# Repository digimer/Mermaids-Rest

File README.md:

# Mermaids-Rest

All tools for the Mermaid's Rest open sailing tools

*Note*: Patches and PRs are welcome, but at this stage of the project, I need to be able to understand / fix the code. Good comments and references to reading material will be grately appreciated! ^_^ 

If/when the project gets outside interest, I'll step out of the way of the much more talented folks.

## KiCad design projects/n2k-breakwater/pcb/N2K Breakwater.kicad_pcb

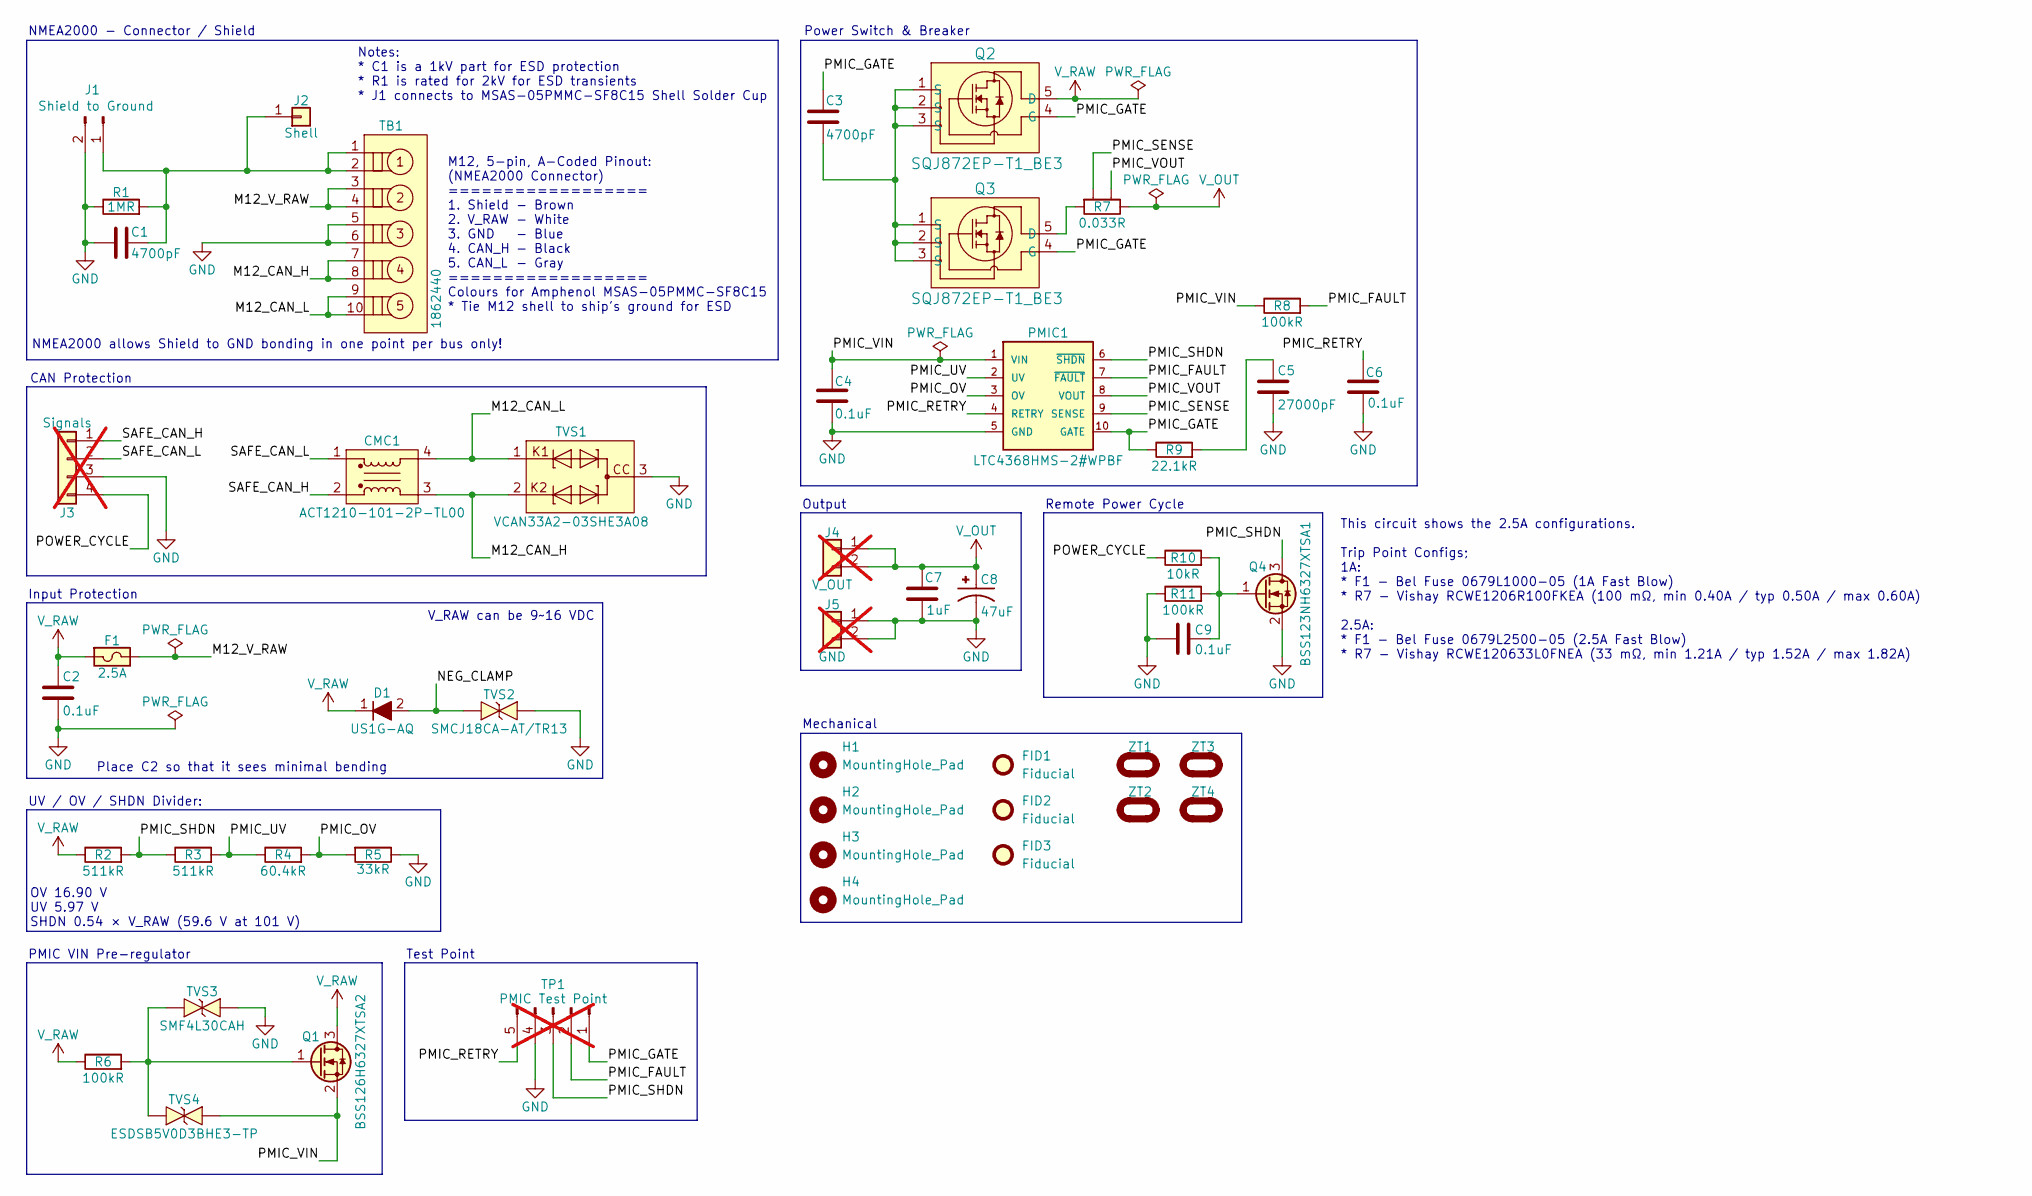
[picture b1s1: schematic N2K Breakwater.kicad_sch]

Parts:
C1, C3: 4700pF; Murata GCJ31BR73A; Part Murata GCJ31BR73A472KXJ1L
C2: 0.1uF; TDK CGA5; Part TDK CGA5L3X7R2E104K160AE
C4, C6, C9: 0.1uF; Kyocera AVX 0805; Part Kyocera 08051C104K4Z2A
C5: 27000pF; Murata GCM0805; Part Murata GCM21B5C2A273JE02K
C7: 1uF; Kyocera AVX 0805; Part Kyocera 08051C105K4Z2A
C8: 47uF; Nichicon PCM; Part Nichicon PCM1V470MCL1GS
CMC1: ACT1210-101-2P-TL00; TDK ACT12101012PTL00; Part TDK ACT1210-101-2P-TL00
D1: US1G-AQ; Diotec US1G; Part Diotec US1G-AQ
F1: 2.5A; Bel Fuse 0679L; Part Bel Fuse 0679L2500-05
FID1, FID2, FID3: Fiducial; Fiducial_1mm_Mask2mm
H1, H2, H3, H4: MountingHole_Pad; MountingHole_4mm
J1: Shield to Ground; PinHeader_1x02_P2.54mm_Vertical
J2: Shell; PinHeader_1x01_P2.54mm_Vertical
J3: Signals; PinHeader_1x04_P2.54mm_Vertical; not fitted
J4: V_OUT; PinHeader_1x02_P2.54mm_Vertical; not fitted
J5: GND; PinHeader_1x02_P2.54mm_Vertical; not fitted
PMIC1: LTC4368HMS-2#WPBF; ADI LTC4368; Part ADI LTC4368HMS-2#WPBF
Q1: BSS126H6327XTSA2; Infineon BSS126; Part Infineon BSS126H6327XTSA2
Q2, Q3: SQJ872EP-T1_BE3; Vishay SQJ872EP; Part Vishay SQJ872EP-T1_BE3
Q4: BSS123NH6327XTSA1; Infineon BSS123; Part Infineon BSS123NH6327XTSA1
R1: 1MR; Stackpole RMCA0805; Part Stackpole RMCA0805FT1M00-HP
R2, R3: 511kR; Vishay RCA e3; Part Vishay RCA0603511KFKEA
R4: 60.4kR; Vishay RCA-SR e3; Part Vishay RCA080560K4FKEA
R5: 33kR; Stackpole RMCA0603; Part Stackpole RMCA0603FT33K0-HP
R6, R8, R11: 100kR; Stackpole RMCA0805; Part Stackpole RMCA0805FT100K-HP
R7: 0.033R; Vishay RCWE 1206 4-wire Kelvin; Part Vishay RCWE120633L0FNEA
R9: 22.1kR; Stackpole RNCP0805; Part Stackpole RNCP0805FTD22K1
R10: 10kR; Stackpole RNCP0805; Part Stackpole RNCP0805FTD10K0
TB1: 1862440; Phoenix Contact 1862440; Part Phoenix Contact 1862440
TP1: PMIC Test Point; PinHeader_1x05_P2.54mm_Vertical; not fitted
TVS1: VCAN33A2-03SHE3A08; Vishay VCAN33A2-03S; Part Vishay VCAN33A2-03SHE3A08
TVS2: SMCJ18CA-AT/TR13; Yageo DO-214AB; Part Yageo SMCJ18CA-AT/TR13
TVS3: SMF4L30CAH; TSC SMF4L30CAH; Part TSC SMF4L30CAH
TVS4: ESDSB5V0D3BHE3-TP; MCC ESDSB5V0D3; Part MCC ESDSB5V0D3BHE3-TP
ZT1, ZT2, ZT3, ZT4: Tuskar Ziptie Slot 4.5x2mm

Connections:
/M12_CAN_H: CMC1.3 (O2), TB1.7, TB1.8, TVS1.2
/M12_CAN_L: CMC1.4 (O1), TB1.9, TB1.10, TVS1.1
/M12_V_RAW: F1.2, TB1.3, TB1.4
/NEG_CLAMP: D1.2 (A), TVS2.1
/PMIC_FAULT: PMIC1.7 (~FAULT), R8.2, TP1.2
/PMIC_GATE: C3.2, PMIC1.10 (GATE), Q2.4 (G), Q3.4 (G), R9.1, TP1.1
/PMIC_OV: PMIC1.3 (OV), R4.2, R5.1
/PMIC_RETRY: C6.2, PMIC1.4 (RETRY), TP1.5
/PMIC_SENSE: PMIC1.9 (SENSE), R7.3
/PMIC_SHDN: PMIC1.6 (~SHDN), Q4.3 (D), R2.2, R3.1, TP1.3
/PMIC_UV: PMIC1.2 (UV), R3.2, R4.1
/PMIC_VIN: C4.1, PMIC1.1 (VIN), Q1.2 (S), R8.1, TVS4.2
/PMIC_VOUT: PMIC1.8 (VOUT), R7.4
/POWER_CYCLE: J3.4, R10.1
/SAFE_CAN_H: CMC1.2 (I2), J3.1
/SAFE_CAN_L: CMC1.1 (I1), J3.2
GND: C1.1, C2.2, C4.2, C5.2, C6.1, C7.2, C8.2, C9.1, J1.2, J3.3, J5.1, J5.2, PMIC1.5 (GND), Q4.2 (S), R1.1, R5.2, R11.1, TB1.5, TB1.6, TP1.4, TVS1.3, TVS2.2, TVS3.2
unnamed: C3.1, Q2.1 (S), Q2.2 (S), Q2.3 (S), Q3.1 (S), Q3.2 (S), Q3.3 (S)
unnamed: C5.1, R9.2
unnamed: C1.2, J1.1, J2.1 (Pin_1_1), R1.2, TB1.1, TB1.2
unnamed: Q1.1 (G), R6.2, TVS3.1, TVS4.1
unnamed: Q3.5 (D), R7.1
unnamed: C9.2, Q4.1 (G), R10.2, R11.2
V_OUT: C7.1, C8.1, J4.1, J4.2, R7.2
V_RAW: C2.1, D1.1 (K), F1.1, Q1.3 (D), Q2.5 (D), R2.1, R6.1

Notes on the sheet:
Remote Power Cycle
CAN Protection
This circuit shows the 2.5A configurations. Trip Point Configs; 1A: * F1 - Bel Fuse 0679L1000-05 (1A Fast Blow) * R7 - Vishay RCWE1206R100FKEA (100 mΩ, min 0.40A / typ 0.50A / max 0.60A) 2.5A: * F1 - Bel Fuse 0679L2500-05 (2.5A Fast Blow) * R7 - Vishay RCWE120633L0FNEA (33 mΩ, min 1.21A / typ 1.52A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
V_RAW can be 9~16 VDC
PMIC VIN Pre-regulator
Output
Notes: * C1 is a 1kV part for ESD protection * R1 is rated for 2kV for ESD transients * J1 connects to MSAS-05PMMC-SF8C15 Shell Solder Cup
M12, 5-pin, A-Coded Pinout: (NMEA2000 Connector) ================== 1. Shield 2. V_RAW 3. GND 4. CAN_H 5. CAN_L ================== Colours for Amphenol MSAS-05PMMC-SF8C15 * Tie M12 shell to ship's ground for ESD
Input Protection
Power Switch & Breaker
UV / OV / SHDN Divider:
Place C2 so that it sees minimal bending
NMEA2000 - Connector / Shield
Mechanical
NMEA2000 allows Shield to GND bonding in one point per bus only!
OV 16.90 V UV 5.97 V SHDN 0.54 × V_RAW (59.6 V at 101 V)
- Brown - White - Blue - Black - Gray
Test Point

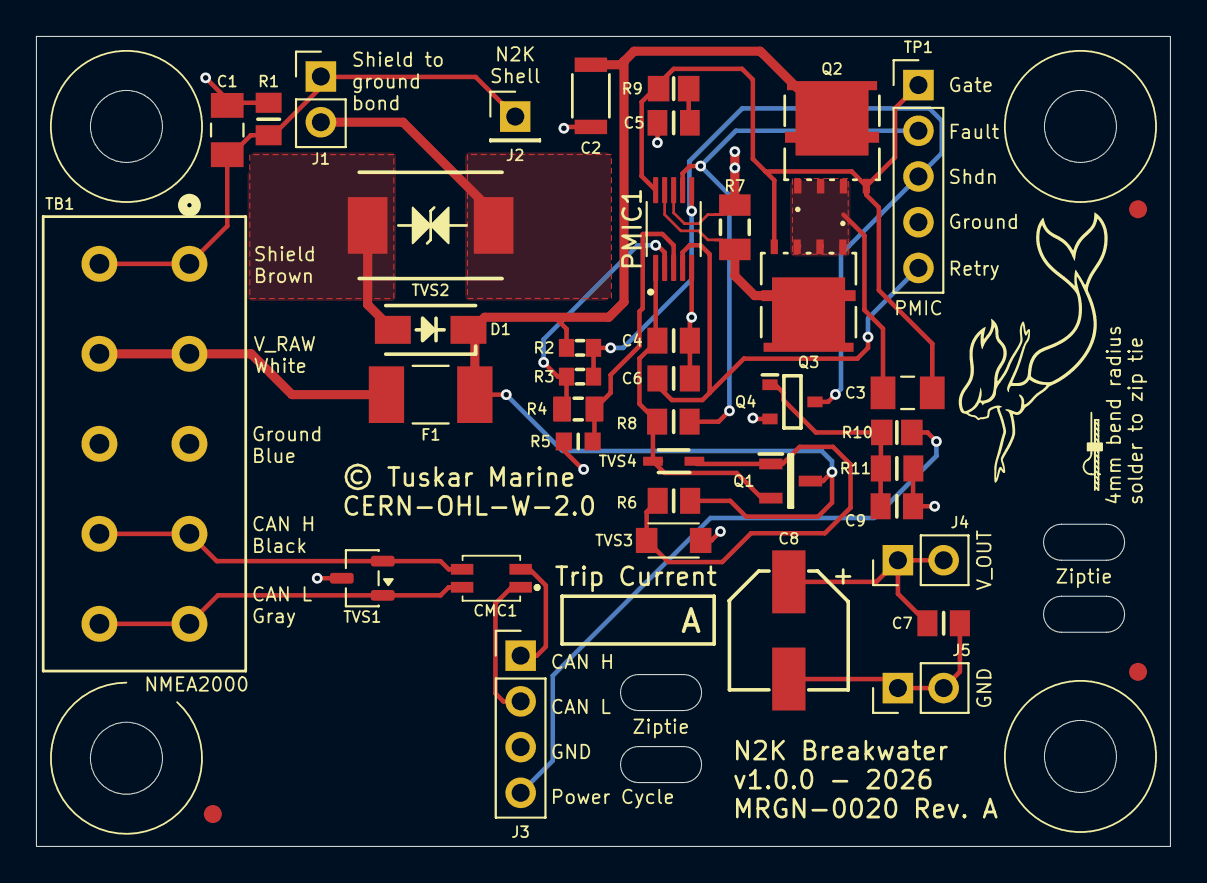
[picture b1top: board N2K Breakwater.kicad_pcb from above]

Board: 4 copper layers, 63.0 x 45.0 mm, 50 parts (0 on the bottom side), 25 nets.

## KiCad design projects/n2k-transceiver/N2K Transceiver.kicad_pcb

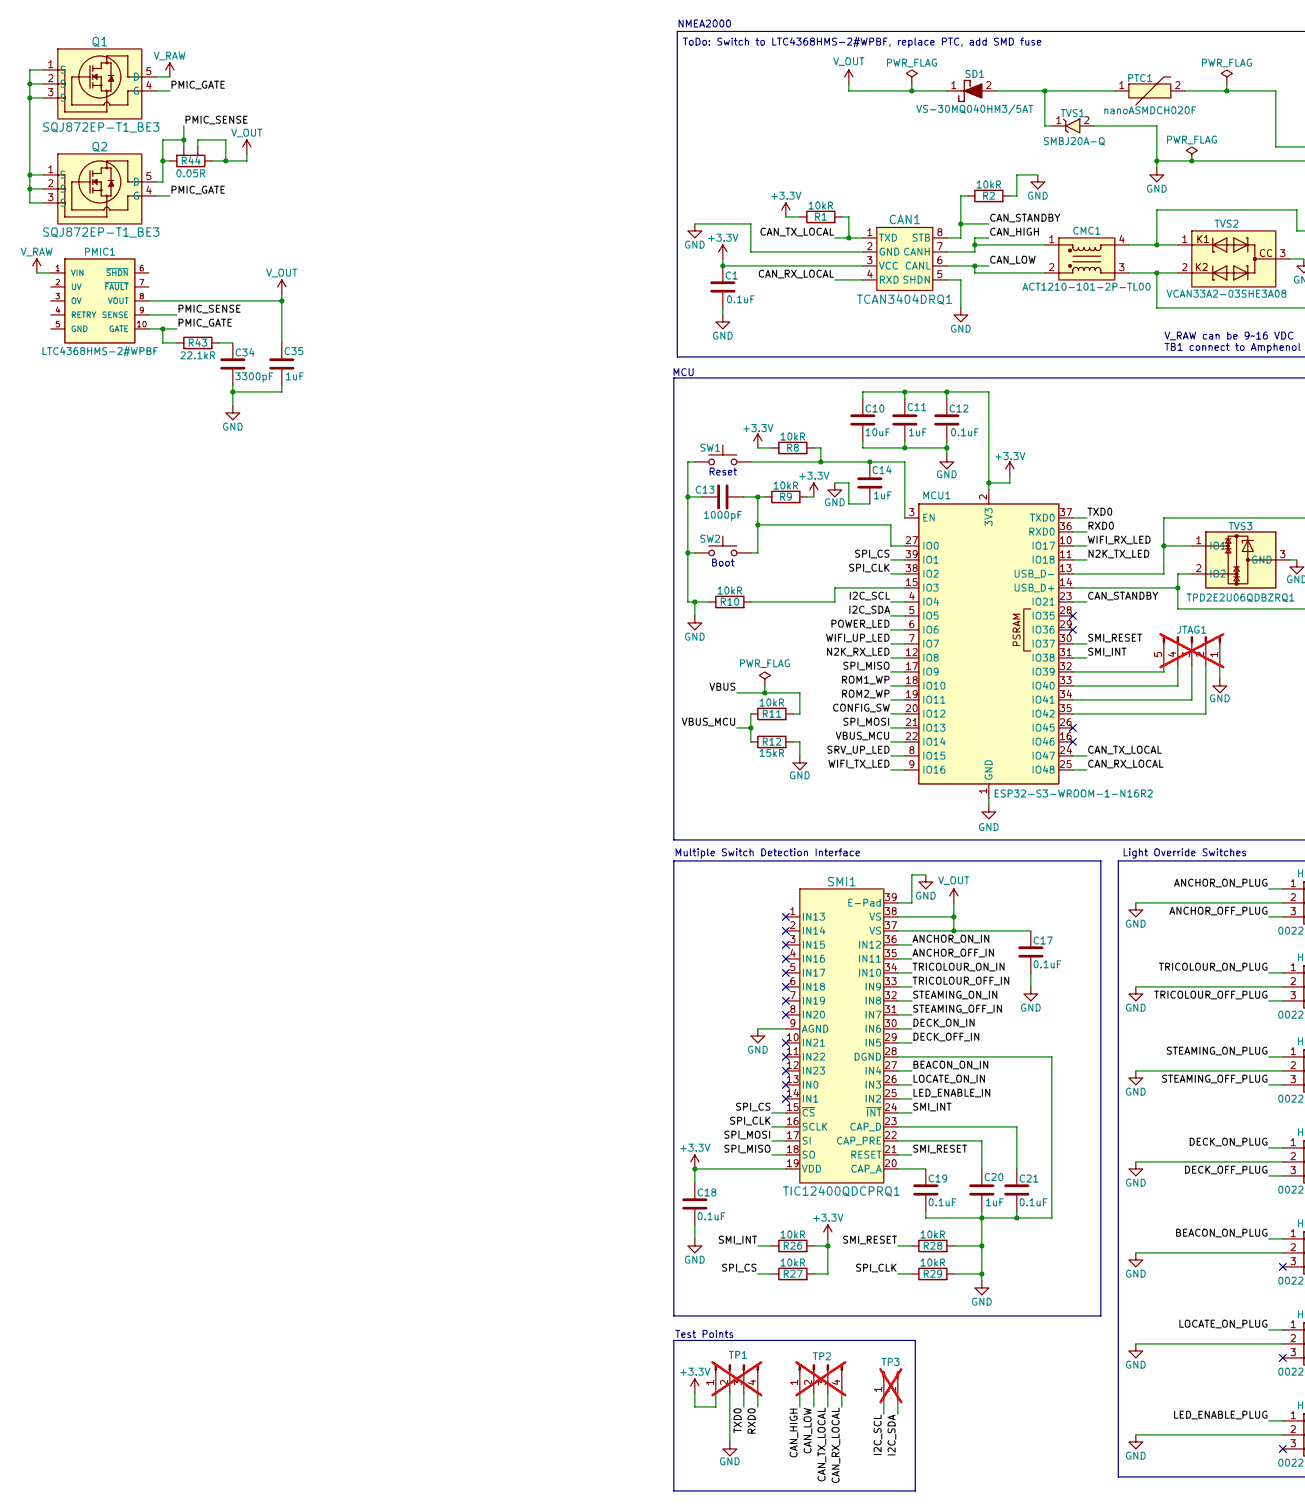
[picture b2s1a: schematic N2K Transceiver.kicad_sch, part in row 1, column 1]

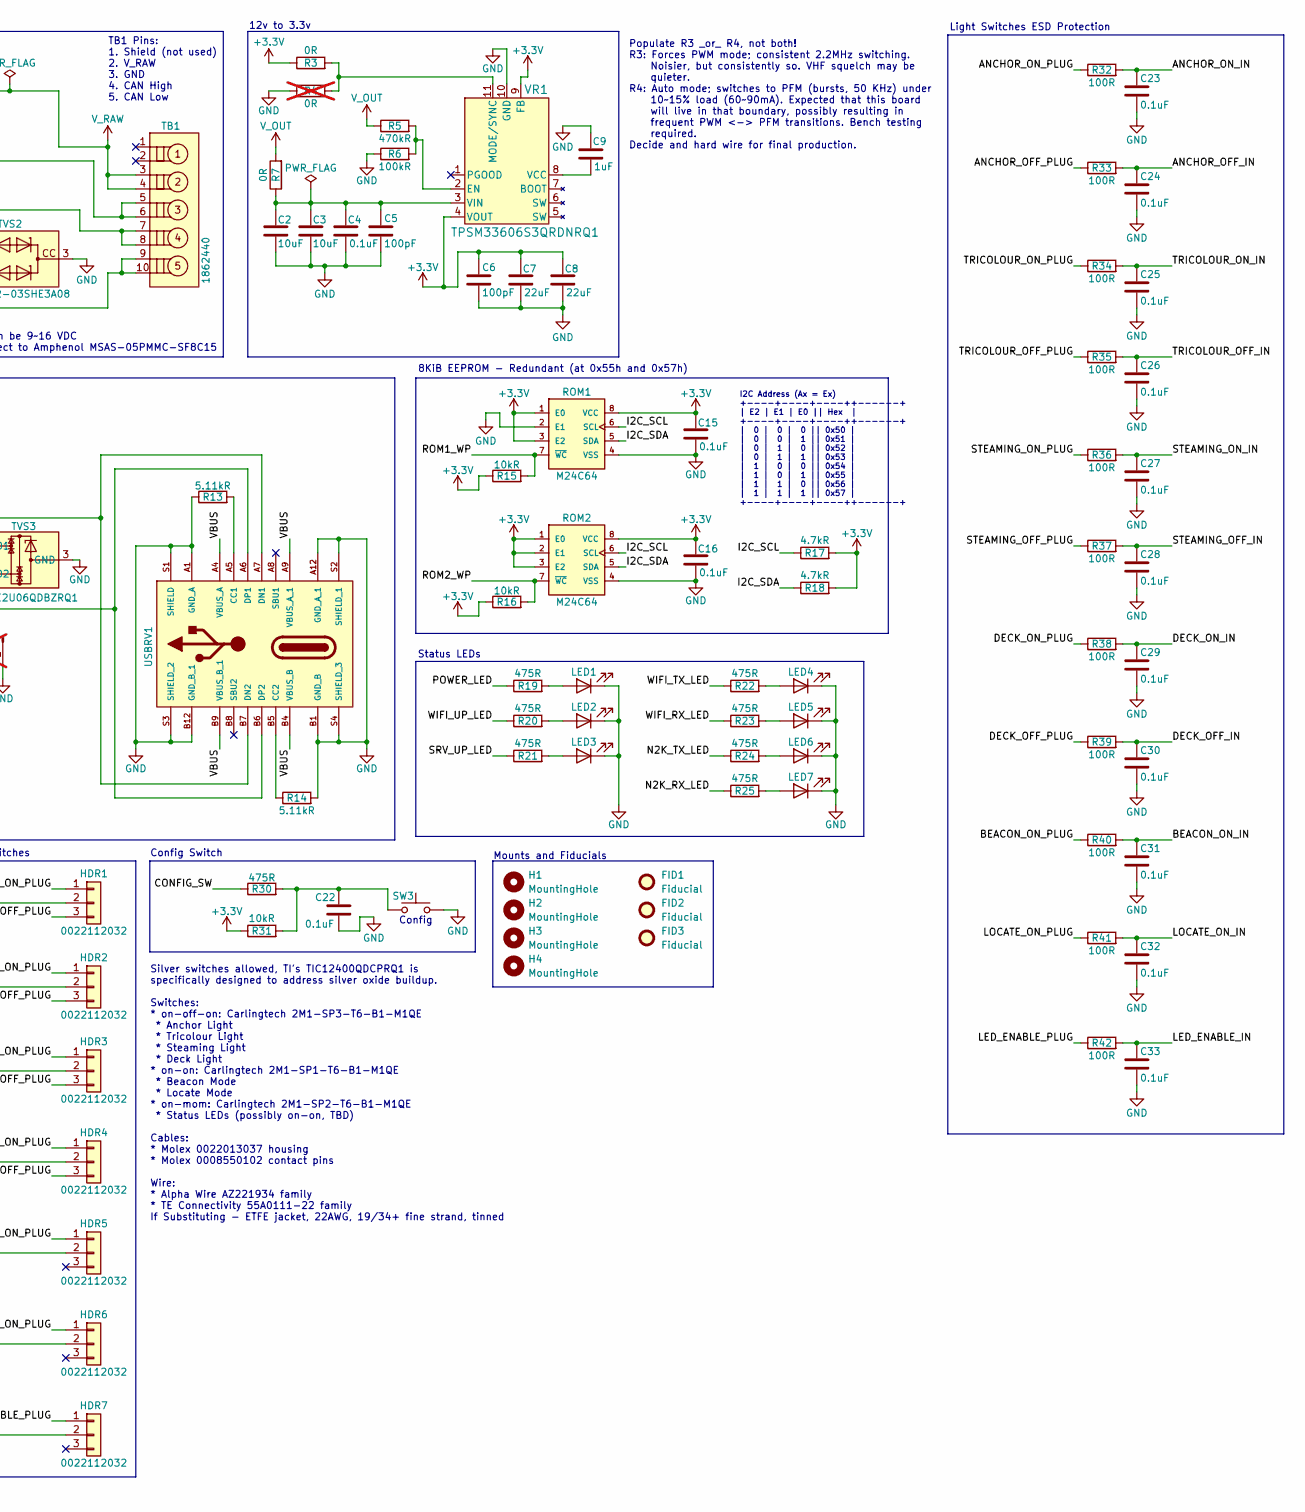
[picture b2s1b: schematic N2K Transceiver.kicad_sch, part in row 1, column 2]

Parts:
C1, C4, C12, C15, C16, C17, C18, C19, C21, C22, C23, C24, C25, C26, C27, C28, C29, C30, C31, C32, C33: 0.1uF; Kyocera AVX 0805; Part Kyocera 08051C104K4Z2A
C2, C3, C10: 10uF; TDK CGA5; Part TDK CGA5L1X7R1H106K160AE
C5, C6: 100pF; Kemet C0805X; Part Kemet C0805X101J5GACAUTO
C7, C8: 22uF; Murata GCJ32ER71C; Part Murata GCJ32ER71C226KE01L
C9, C11, C14, C20, C35: 1uF; Kyocera AVX 0805; Part Kyocera 08051C105K4Z2A
C13: 1000pF; TDK CGA 0805; Part TDK CGA4F2X7R2A102K085AE
C34: 3300pF; TDK CGA 0805; Part TDK CGA3E1C0G2A332J080AE
CAN1: TCAN3404DRQ1; TI TCAN3404; Part TI TCAN3404DRQ1
CMC1: ACT1210-101-2P-TL00; TDK ACT12101012PTL00; Part TDK ACT1210-101-2P-TL00
FID1, FID2, FID3: Fiducial; Fiducial_1mm_Mask2mm
H1, H2, H3, H4: MountingHole; MountingHole_4.3mm_M4
HDR1, HDR2, HDR3, HDR4, HDR5, HDR6, HDR7: 0022112032; Molex 0022112032; Part Molex 0022112032
JTAG1: Conn_01x05_Pin; PinHeader_1x05_P2.54mm_Vertical; not fitted
LED1, LED2, LED3, LED4, LED5, LED6, LED7: TLMS1101-GS15; Vishay TLMS1101; Part Vishay TLMS1101-GS15
MCU1: ESP32-S3-WROOM-1-N16R2; Espressif ESP32-S3; Part Espressif ESP32-S3-WROOM-1-N16R2
PMIC1: LTC4368HMS-2#WPBF; ADI LTC4368; Part ADI LTC4368HMS-2#WPBF
PTC1: nanoASMDCH020F; Littelfuse NANOASMDCH020F; Part Littelfuse nanoASMDCH020F
Q1, Q2: SQJ872EP-T1_BE3; Vishay SQJ872EP; Part Vishay SQJ872EP-T1_BE3
R1, R2, R8, R9, R10, R11, R15, R16, R26, R27, R28, R29, R31: 10kR; Stackpole RNCP0805; Part Stackpole RNCP0805FTD10K0
R3, R7: 0R; Vishay RCA-SR e3; Part Vishay RCA08050000ZSEASR
R4: 0R; Vishay RCA-SR e3; Part Vishay RCA08050000ZSEASR; not fitted
R5: 470kR; Wurth WRIS-RSKS; Part Wurth 560112120009
R6: 100kR; Stackpole RMCA0805; Part Stackpole RMCA0805FT100K-HP
R12: 15kR; Stackpole RNCP0805; Part Stackpole RNCP0805FTD15K0
R13, R14: 5.11kR; Stackpole RNCP0805; Part Stackpole RNCP0805FTD5K11
R17, R18: 4.7kR; Stackpole RMCA0805; Part Stackpole RMCA0805FT4K70-HP
R19, R20, R21, R22, R23, R24, R25, R30: 475R; Stackpole RNCP0805; Part Stackpole RNCP0805FTD475R
R32, R33, R34, R35, R36, R37, R38, R39, R40, R41, R42: 100R; Stackpole RNCP0805; Part Stackpole RNCP0805FTD100R
R43: 22.1kR; Stackpole RNCP0805; Part Stackpole RNCP0805FTD22K1
R44: 0.05R; Vishay WSLP 1206 4-wire Kelvin; Part Vishay WSLP1206R0500FEA
ROM1, ROM2: M24C64; STM M24C64-RMN6P; Part STM M24C64-RMN6P
SD1: VS-30MQ040HM3/5AT; Vishay 30MQ040; Part Vishay VS-30MQ040HM3/5AT
SMI1: TIC12400QDCPRQ1; TI TIC12400QDCPRQ1; Part TI TIC12400QDCPRQ1
SW1, SW2, SW3: TS03-66-50-BK-160-LCR-D-67; Same Sky TS03-66; Part Same Sky TS03-66-50-BK-160-LCR-D-67
TB1: 1862440; Phoenix Contact 1862440; Part Phoenix Contact 1862440
TP1: Power/UART Test Point; PinHeader_1x04_P2.54mm_Vertical; not fitted
TP2: CAN Test Point; PinHeader_1x04_P2.54mm_Vertical; not fitted
TP3: I2C Test Point; PinHeader_1x02_P2.54mm_Vertical; not fitted
TVS1: SMBJ20A-Q; Bourns SMBJ20; Part Bourns SMBJ20A-Q
TVS2: VCAN33A2-03SHE3A08; Vishay VCAN33A2-03S; Part Vishay VCAN33A2-03SHE3A08
TVS3: TPD2E2U06QDBZRQ1; TI TPD2E2U06; Part TI TPD2E2U06QDBZRQ1
USBRV1: USB4145-03-0170-C; GCT USB4145-03-0170-C; Part GCT USB4145-03-0170-C
VR1: TPSM33606S3QRDNRQ1; TI TPSM336; Part TI TPSM33606S3QRDNRQ1

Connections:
+3.3V: C1.1, C6.1, C7.1, C8.1, C10.1, C11.1, C12.1, C15.1, C16.1, C18.1, CAN1.3 (VCC), MCU1.2 (3V3), R1.1, R3.1, R8.1, R9.2, R15.1, R16.1, R17.2, R18.2, R26.2, R27.2, R31.1, ROM1.1 (E0), ROM1.3 (E2), ROM1.8 (VCC), ROM2.1 (E0), ROM2.2 (E1), ROM2.3 (E2), ROM2.8 (VCC), SMI1.19 (VDD), TP1.1, VR1.4 (VOUT), VR1.9 (FB)
/ANCHOR_OFF_IN: C24.1, R33.2, SMI1.35 (IN11)
/ANCHOR_OFF_PLUG: HDR1.3, R33.1
/ANCHOR_ON_IN: C23.1, R32.2, SMI1.36 (IN12)
/ANCHOR_ON_PLUG: HDR1.1, R32.1
/BEACON_ON_IN: C31.1, R40.2, SMI1.27 (IN4)
/BEACON_ON_PLUG: HDR5.1, R40.1
/CAN_HIGH: CAN1.7 (CANH), CMC1.1 (I1), TP2.1
/CAN_LOW: CAN1.6 (CANL), CMC1.2 (I2), TP2.2
/CAN_RX_LOCAL: CAN1.4 (RXD), MCU1.25 (IO48), TP2.4
/CAN_STANDBY: CAN1.8 (STB), MCU1.23 (IO21), R2.1
/CAN_TX_LOCAL: CAN1.1 (TXD), MCU1.24 (IO47), R1.2, TP2.3
/CONFIG_SW: MCU1.20 (IO12), R30.1
/DECK_OFF_IN: C30.1, R39.2, SMI1.29 (IN5)
/DECK_OFF_PLUG: HDR4.3, R39.1
/DECK_ON_IN: C29.1, R38.2, SMI1.30 (IN6)
/DECK_ON_PLUG: HDR4.1, R38.1
/I2C_SCL: MCU1.4 (IO4), R17.1, ROM1.6 (SCL), ROM2.6 (SCL), TP3.1
/I2C_SDA: MCU1.5 (IO5), R18.1, ROM1.5 (SDA), ROM2.5 (SDA), TP3.2
/LED_ENABLE_IN: C33.1, R42.2, SMI1.25 (IN2)
/LED_ENABLE_PLUG: HDR7.1, R42.1
/LOCATE_ON_IN: C32.1, R41.2, SMI1.26 (IN3)
/LOCATE_ON_PLUG: HDR6.1, R41.1
/N2K_RX_LED: MCU1.12 (IO8), R25.1
/N2K_TX_LED: MCU1.11 (IO18), R24.1
/POWER_LED: MCU1.6 (IO6), R19.1
/ROM1_WP: MCU1.18 (IO10), R15.2, ROM1.7 (~WC)
/ROM2_WP: MCU1.19 (IO11), R16.2, ROM2.7 (~WC)
/RXD0: MCU1.36 (RXD0), TP1.4
/SMI_INT: MCU1.31 (IO38), R26.1, SMI1.24 (~INT)
/SMI_RESET: MCU1.30 (IO37), R28.1, SMI1.21 (RESET)
/SPI_CLK: MCU1.38 (IO2), R29.1, SMI1.16 (SCLK)
/SPI_CS: MCU1.39 (IO1), R27.1, SMI1.15 (~CS)
/SPI_MISO: MCU1.17 (IO9), SMI1.18 (SO)
/SPI_MOSI: MCU1.21 (IO13), SMI1.17 (SI)
/SRV_UP_LED: MCU1.8 (IO15), R21.1
/STEAMING_OFF_IN: C28.1, R37.2, SMI1.31 (IN7)
/STEAMING_OFF_PLUG: HDR3.3, R37.1
/STEAMING_ON_IN: C27.1, R36.2, SMI1.32 (IN8)
/STEAMING_ON_PLUG: HDR3.1, R36.1
/TRICOLOUR_OFF_IN: C26.1, R35.2, SMI1.33 (IN9)
/TRICOLOUR_OFF_PLUG: HDR2.3, R35.1
/TRICOLOUR_ON_IN: C25.1, R34.2, SMI1.34 (IN10)
/TRICOLOUR_ON_PLUG: HDR2.1, R34.1
/TXD0: MCU1.37 (TXD0), TP1.3
/VBUS: R11.2, USBRV1.A4 (VBUS_A), USBRV1.A9 (VBUS_A_1), USBRV1.B4 (VBUS_B), USBRV1.B9 (VBUS_B_1)
/VBUS_MCU: MCU1.22 (IO14), R11.1, R12.1
/WIFI_RX_LED: MCU1.10 (IO17), R23.1
/WIFI_TX_LED: MCU1.9 (IO16), R22.1
/WIFI_UP_LED: MCU1.7 (IO7), R20.1
GND: C1.2, C2.2, C3.2, C4.2, C5.2, C6.2, C7.2, C8.2, C9.1, C10.2, C11.2, C12.2, C13.1, C14.2, C15.2, C16.2, C17.2, C18.2, C19.2, C20.2, C21.2, C22.1, C23.2, C24.2, C25.2, C26.2, C27.2, C28.2, C29.2, C30.2, C31.2, C32.2, C33.2, C34.2, C35.2, CAN1.2 (GND), CAN1.5 (SHDN), HDR1.2, HDR2.2, HDR3.2, HDR4.2, HDR5.2, HDR6.2, HDR7.2, JTAG1.1, LED1.1 (K), LED2.1 (K), LED3.1 (K), LED4.1 (K), LED5.1 (K), LED6.1 (K), LED7.1 (K), MCU1.1 (GND), MCU1.40 (GND), MCU1.41 (GND), R2.2, R4.2, R6.1, R10.1, R12.2, R13.1, R14.2, R28.2, R29.2, ROM1.2 (E1), ROM1.4 (VSS), ROM2.4 (VSS), SMI1.9 (AGND), SMI1.28 (DGND), SMI1.39 (E-Pad), SW1.1 (A), SW1.2 (A), SW2.1 (A), SW2.2 (A), SW3.3 (B), SW3.4 (B), TB1.5, TB1.6, TP1.2, TVS1.2 (A), TVS2.3, TVS3.3 (GND), USBRV1.A1 (GND_A), USBRV1.A12 (GND_A_1), USBRV1.B1 (GND_B), USBRV1.B12 (GND_B_1), USBRV1.S1 (SHIELD), USBRV1.S2 (SHIELD_1), USBRV1.S3 (SHIELD_2), USBRV1.S4 (SHIELD_3), VR1.10 (GND)
unnamed: C22.2, R30.2, R31.2, SW3.1 (A), SW3.2 (A)
unnamed: C34.1, R43.2
unnamed: CMC1.4 (O1), TB1.7, TB1.8, TVS2.1
unnamed: CMC1.3 (O2), TB1.9, TB1.10, TVS2.2
unnamed: JTAG1.2, MCU1.35 (IO42)
unnamed: JTAG1.3, MCU1.34 (IO41)
unnamed: JTAG1.4, MCU1.33 (IO40)
unnamed: JTAG1.5, MCU1.32 (IO39)
unnamed: LED1.2 (A), R19.2
unnamed: LED2.2 (A), R20.2
unnamed: LED3.2 (A), R21.2
unnamed: LED4.2 (A), R22.2
unnamed: LED5.2 (A), R23.2
unnamed: LED6.2 (A), R24.2
unnamed: LED7.2 (A), R25.2
unnamed: C14.1, MCU1.3 (EN), R8.2, SW1.3 (B), SW1.4 (B)
unnamed: C13.2, MCU1.27 (IO0), R9.1, SW2.3 (B), SW2.4 (B)
unnamed: MCU1.15 (IO3), R10.2
unnamed: MCU1.14 (USB_D+), TVS3.2 (IO2), USBRV1.A6 (DP1), USBRV1.B6 (DP2)
unnamed: MCU1.13 (USB_D-), TVS3.1 (IO1), USBRV1.A7 (DN1), USBRV1.B7 (DN2)
unnamed: PMIC1.9 (SENSE), Q2.5 (D), R44.1, R44.3
unnamed: PMIC1.10 (GATE), Q1.4 (G), Q2.4 (G), R43.1
unnamed: PMIC1.1 (VIN), PTC1.2, Q1.5 (D), TB1.3, TB1.4
unnamed: Q1.1 (S), Q1.2 (S), Q1.3 (S), Q2.1 (S), Q2.2 (S), Q2.3 (S)
unnamed: PTC1.1, SD1.2 (A), TVS1.1 (K)
unnamed: C19.1, SMI1.20 (CAP_A)
unnamed: C21.1, SMI1.23 (CAP_D)
unnamed: C20.1, SMI1.22 (CAP_PRE)
unnamed: R13.2, USBRV1.A5 (CC1)
unnamed: R14.1, USBRV1.B5 (CC2)
unnamed: R5.2, R6.2, VR1.2 (EN)
unnamed: R3.2, R4.1, VR1.11 (MODE/SYNC)
unnamed: C9.2, VR1.8 (VCC)
unnamed: C2.1, C3.1, C4.1, C5.1, R7.1, VR1.3 (VIN)
V_RAW: C17.1, C35.1, PMIC1.8 (VOUT), R5.1, R7.2, R44.2, R44.4, SD1.1 (K), SMI1.37 (VS), SMI1.38 (VS)

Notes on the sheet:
V_RAW can be 9~16 VDC TB1 connect to Amphenol MSAS-05PMMC-SF8C15
Config Switch
MCU
Silver switches allowed, TI's TIC12400QDCPRQ1 is specifically designed to address silver oxide buildup. Switches: * on-off-on: Carlingtech 2M1-SP3-T6-B1-M1QE * Anchor Light * Tricolour Light * Steaming Light * Deck Light * on-on: Carlingtech 2M1-SP1-T6-B1-M1QE * Beacon Mode * Locate Mode * on-mom: 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
Multiple Switch Detection Interface
Mounts and Fiducials
Test Points
Boot
Light Override Switches
Status LEDs
NMEA2000
I2C Address (Ax = Ex) +----+----+----++------+ | E2 | E1 | E0 || Hex | +----+----+----++------+ | 0 | 0 | 0 || 0x50 | | 0 | 0 | 1 || 0x51 | | 0 | 1 | 0 || 0x52 | | 0 | 1 | 1 || 0x53 | | 1 | 0 | 0 || 0x54 | | 1 | 0 | 1 || 0x55 | | 1 | 1 | 0 || 0x56 | | 1 | 1 | 1 || 0x57 | +----+----+----++------+
Config
Reset
Populate R3 _or_ R4, not both! R3: Forces PWM mode; consistent 2.2MHz switching. Noisier, but consistently so. VHF squelch may be quieter. R4: Auto mode; switches to PFM (bursts, 50 KHz) under 10~15% load (60~90mA). Expected that this board will live in that boundary, possibly resulting in frequent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
TB1 Pins: 1. Shield (not used) 2. V_RAW 3. GND 4. CAN High 5. CAN Low
12v to 3.3v
ToDo: Switch to LTC4368HMS-2#WPBF, replace PTC, add SMD fuse
Light Switches ESD Protection
8KiB EEPROM - Redundant (at 0x55h and 0x57h)

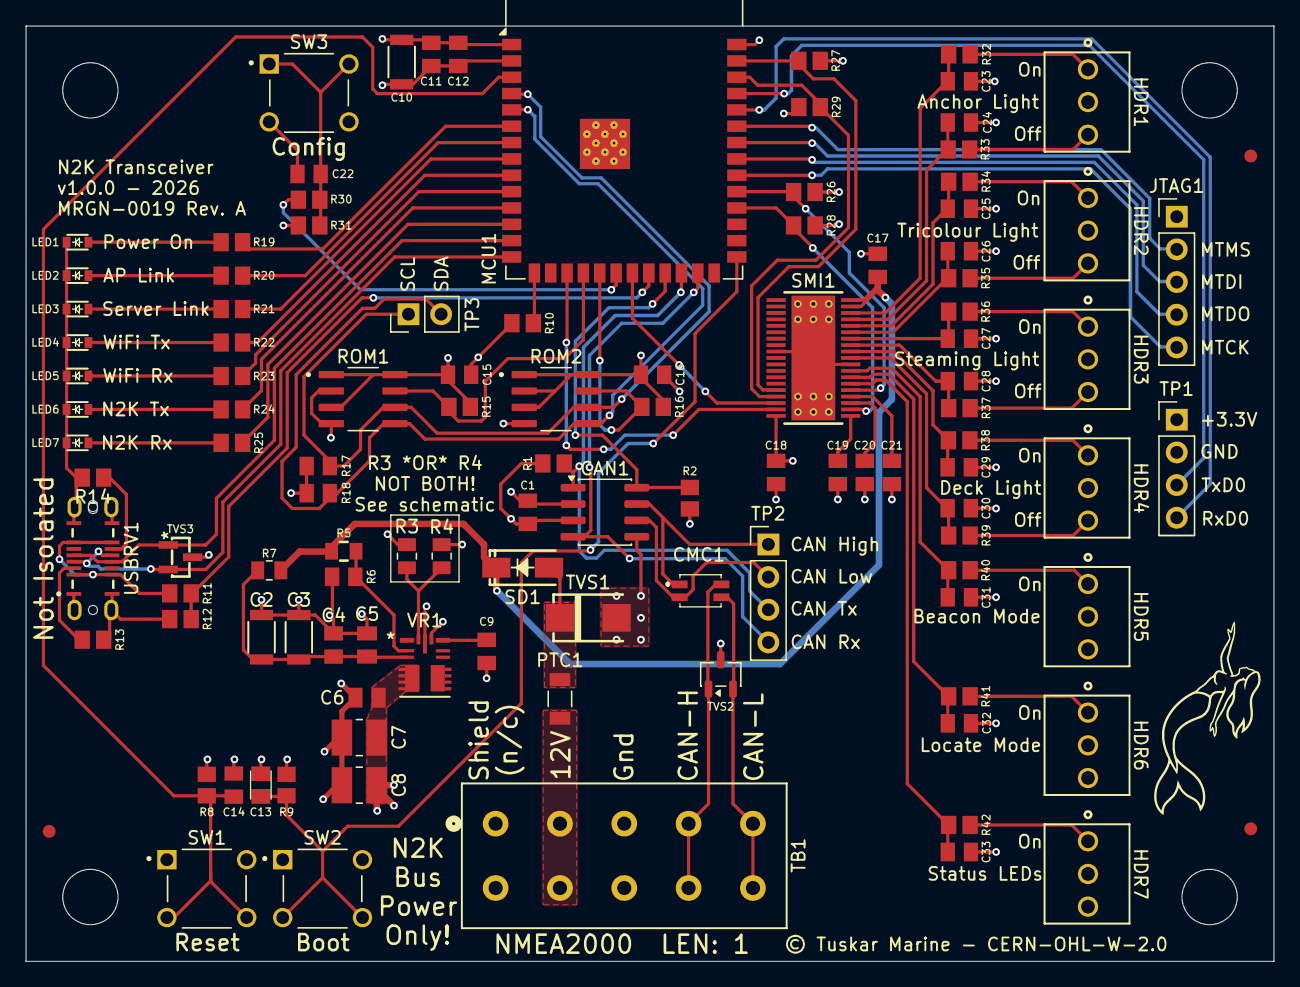
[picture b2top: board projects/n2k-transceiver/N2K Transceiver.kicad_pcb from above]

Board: 4 copper layers, 97.0 x 72.7 mm, 117 parts (0 on the bottom side), 82 nets.

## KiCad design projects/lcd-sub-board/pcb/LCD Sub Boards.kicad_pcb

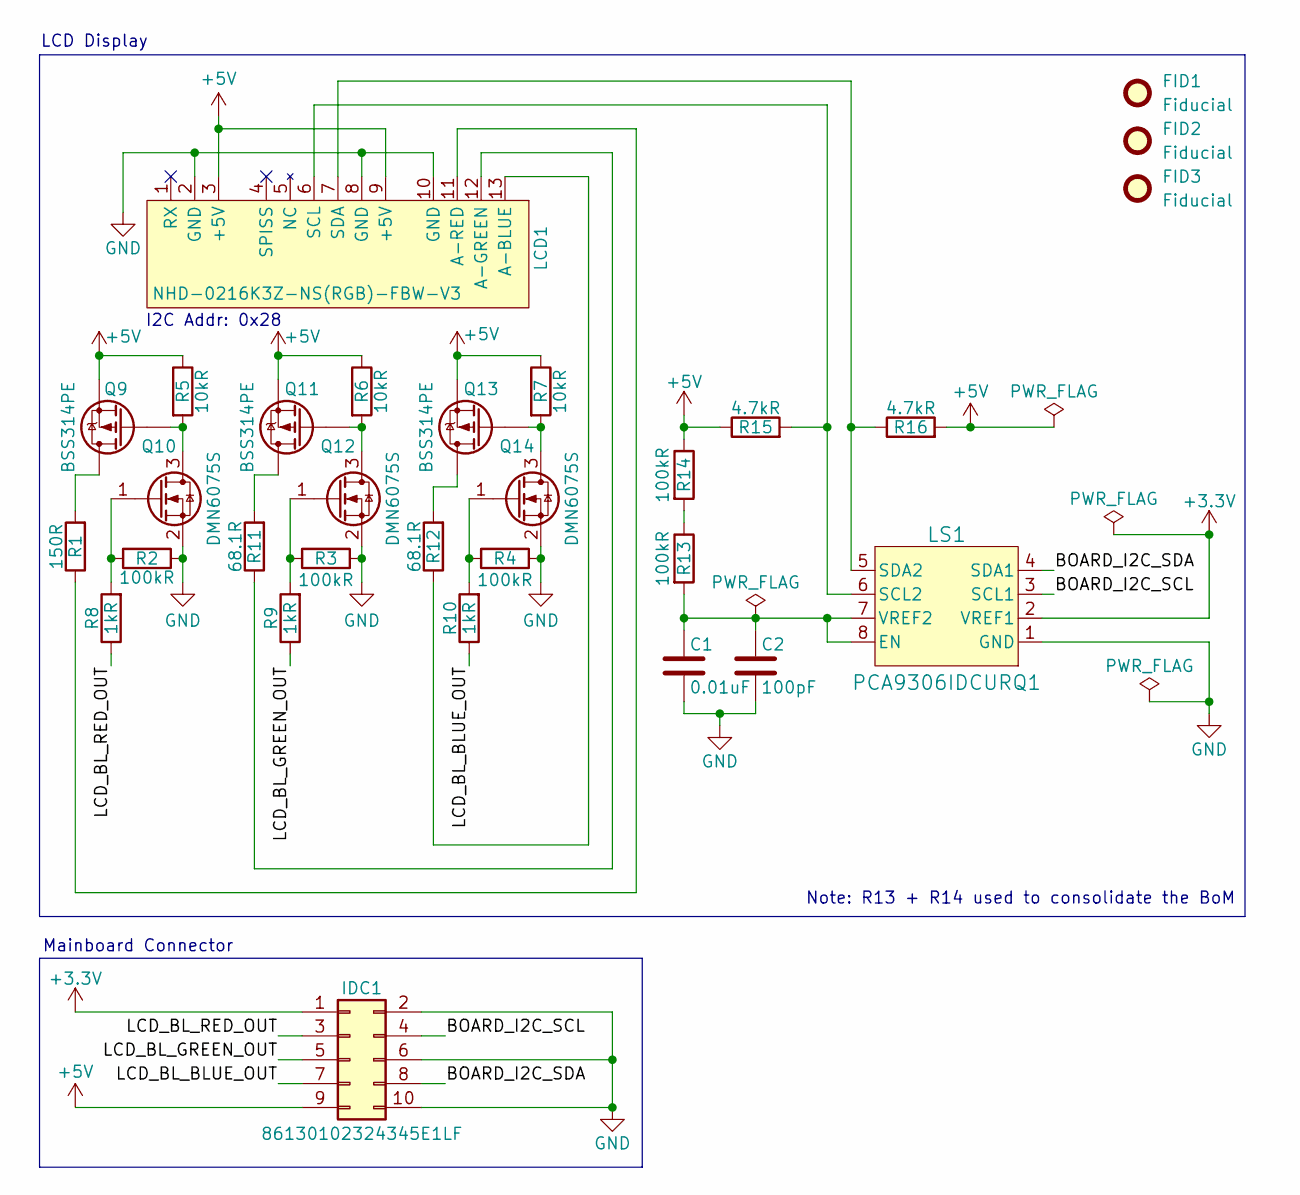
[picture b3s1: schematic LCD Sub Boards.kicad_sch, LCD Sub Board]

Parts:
C1: 0.01uF; Kemet C0805X; Part Kemet C0805X103J1GECAUTO
C2: 100pF; Kemet C0805X; Part Kemet C0805X101J1GACAUTO
FID1, FID2, FID3: Fiducial; Fiducial_1mm_Mask2mm
IDC1: 86130102324345E1LF; Amphenol 86130102324345E1LF; Part Amphenol 86130102324345E1LF
LCD1: NHD-0216K3Z-NS(RGB)-FBW-V3; Newhaven Display NHD-0216K3Z-NS(RGB)-FBW-V3; Part Newhaven Display NHD-0216K3Z-NS(RGB)-FB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
LS1: PCA9306IDCURQ1; TI PCA9306; Part TI PCA9306IDCURQ1
Q9, Q11, Q13: BSS314PE; SOT-23; Part Infineon BSS314PEH6327XTSA1
Q10, Q12, Q14: DMN6075S; SOT-23; Part Diodes Inc DMN6075SQ-7
R1: 150R; Stackpole RNCP0805; Part Stackpole RNCP0805FTD150R
R2, R3, R4, R13, R14: 100kR; Stackpole RMCA0805; Part Stackpole RMCA0805FT100K-HP
R5, R6, R7: 10kR; Stackpole RNCP0805; Part Stackpole RNCP0805FTD10K0
R8, R9, R10: 1kR; Stackpole RNCP0805; Part Stackpole RNCP0805FTD1K00
R11, R12: 68.1R; Stackpole RNCP0805; Part Stackpole RNCP0805FTD68R1
R15, R16: 4.7kR; Stackpole RMCA0805; Part Stackpole RMCA0805FT4K70-HP

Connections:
+3.3V: IDC1.1, LS1.2 (VREF1)
+5V: IDC1.9, LCD1.3 (+5V), LCD1.9 (+5V), Q9.2 (S), Q11.2 (S), Q13.2 (S), R5.1, R6.1, R7.1, R14.1, R15.1, R16.2
/BOARD_I2C_SCL: IDC1.4, LS1.3 (SCL1)
/BOARD_I2C_SDA: IDC1.8, LS1.4 (SDA1)
/LCD_BL_BLUE_OUT: IDC1.7, R10.1
/LCD_BL_GREEN_OUT: IDC1.5, R9.1
/LCD_BL_RED_OUT: IDC1.3, R8.1
GND: C1.2, C2.2, IDC1.2, IDC1.6, IDC1.10, LCD1.2 (GND), LCD1.8 (GND), LCD1.10 (GND), LS1.1 (GND), Q10.2 (S), Q12.2 (S), Q14.2 (S), R2.1, R3.1, R4.1
unnamed: LCD1.13 (A-BLUE), R12.1
unnamed: LCD1.12 (A-GREEN), R11.1
unnamed: LCD1.11 (A-RED), R1.1
unnamed: LCD1.6 (SCL), LS1.6 (SCL2), R15.2
unnamed: LCD1.7 (SDA), LS1.5 (SDA2), R16.1
unnamed: C1.1, C2.1, LS1.7 (VREF2), LS1.8 (EN), R13.2
unnamed: Q9.3 (D), R1.2
unnamed: Q9.1 (G), Q10.3 (D), R5.2
unnamed: Q10.1 (G), R2.2, R8.2
unnamed: Q11.3 (D), R11.2
unnamed: Q11.1 (G), Q12.3 (D), R6.2
unnamed: Q12.1 (G), R3.2, R9.2
unnamed: Q13.3 (D), R12.2
unnamed: Q13.1 (G), Q14.3 (D), R7.2
unnamed: Q14.1 (G), R4.2, R10.2
unnamed: R13.1, R14.2

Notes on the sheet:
I2C Addr: 0x28
LCD Display
Note: R13 + R14 used to consolidate the BoM
Mainboard Connector

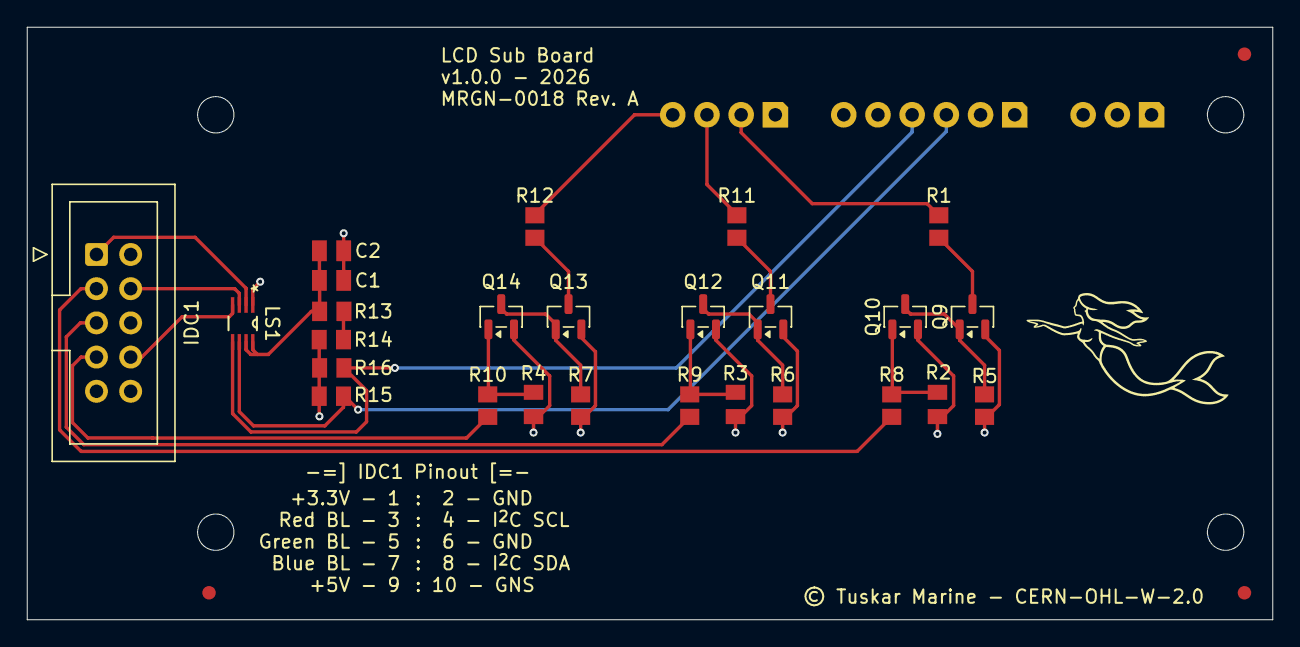
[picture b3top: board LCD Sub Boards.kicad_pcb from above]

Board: 4 copper layers, 92.5 x 44.0 mm, 30 parts (1 on the bottom side), 24 nets.

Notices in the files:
Full Boards/Battery Display/Battery Display.kicad_pcb:
© The Digital Mermaid - 2026
CERN Open Hardware Licence
Full Boards/Masthead Controller/Masthead Controller.kicad_pcb:
© Tuskar Marine - CERN OHL-WR v2
projects/N2K Transceiver/N2K Transceiver.kicad_pcb:
CERN OHL-WR
projects/lcd-sub-board/pcb/LCD Sub Boards.kicad_pcb:
© Tuskar Marine - CERN-OHL-W-2.0
projects/n2k-breakwater/pcb/N2K Breakwater.kicad_pcb:
CERN-OHL-W-2.0
